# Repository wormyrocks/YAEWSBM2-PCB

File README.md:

# YAEWSBM2-PCB
PCBA for Dewster's Etherwave Standard bass extension module

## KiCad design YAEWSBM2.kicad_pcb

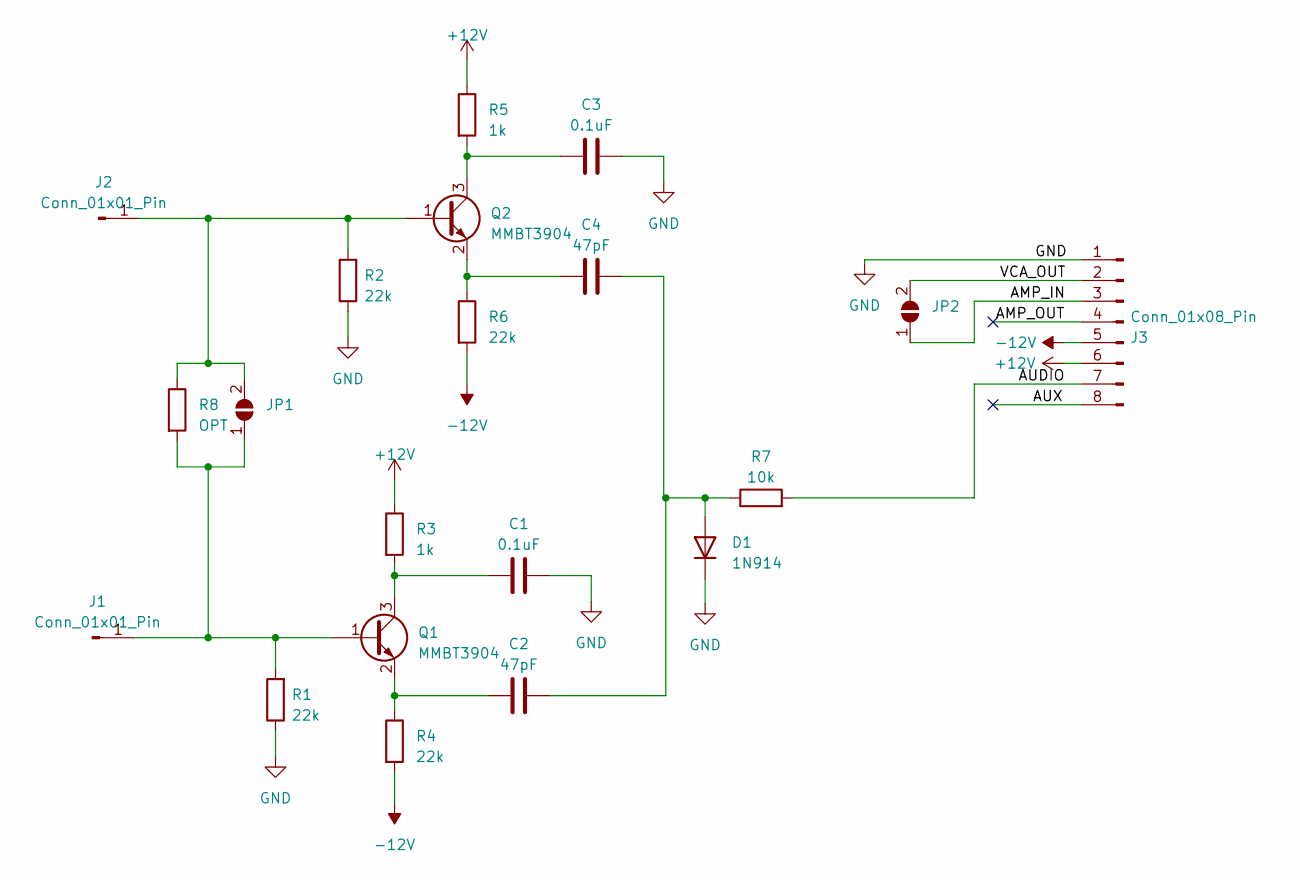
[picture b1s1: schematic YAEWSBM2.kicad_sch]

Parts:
C1, C3: 0.1uF; C_0603_1608Metric_Pad1.08x0.95mm_HandSolder
C2, C4: 47pF; C_0603_1608Metric_Pad1.08x0.95mm_HandSolder
D1: 1N914; D_SOD-523
J1, J2: Conn_01x01_Pin; PinHeader_1x01_P2.54mm_Vertical
J3: Conn_01x08_Pin; PinHeader_1x08_P2.54mm_Vertical
JP1, JP2: SolderJumper_2_Open; SolderJumper-2_P1.3mm_Open_RoundedPad1.0x1.5mm
Q1, Q2: MMBT3904; SOT-23
R1, R2, R4, R6: 22k; R_0603_1608Metric_Pad0.98x0.95mm_HandSolder
R3, R5: 1k; R_0603_1608Metric_Pad0.98x0.95mm_HandSolder
R7: 10k; R_0603_1608Metric_Pad0.98x0.95mm_HandSolder
R8: OPT; R_Axial_DIN0204_L3.6mm_D1.6mm_P5.08mm_Horizontal

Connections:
+12V: J3.6, R3.1, R5.1
-12V: J3.5, R4.2, R6.2
/AMP_IN: J3.3, JP2.1 (A)
/AMP_OUT: J3.4
/AUDIO: J3.7, R7.2
/AUX: J3.8
/VCA_OUT: J3.2, JP2.2 (B)
GND: C1.2, C3.2, D1.1 (K), J3.1, R1.1, R2.1
unnamed: C2.2, C4.2, D1.2 (A), R7.1
unnamed: J1.1, JP1.1 (A), Q1.1 (B), R1.2, R8.2
unnamed: J2.1, JP1.2 (B), Q2.1 (B), R2.2, R8.1
unnamed: C1.1, Q1.3 (C), R3.2
unnamed: C2.1, Q1.2 (E), R4.1
unnamed: C3.1, Q2.3 (C), R5.2
unnamed: C4.1, Q2.2 (E), R6.1

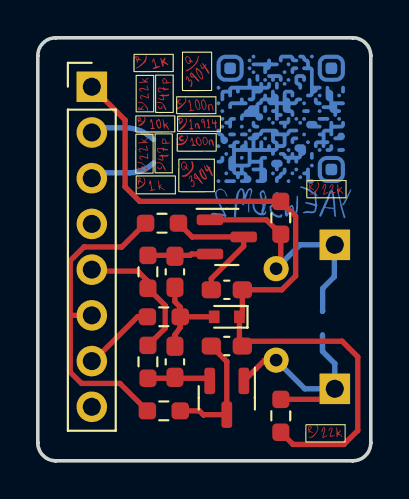
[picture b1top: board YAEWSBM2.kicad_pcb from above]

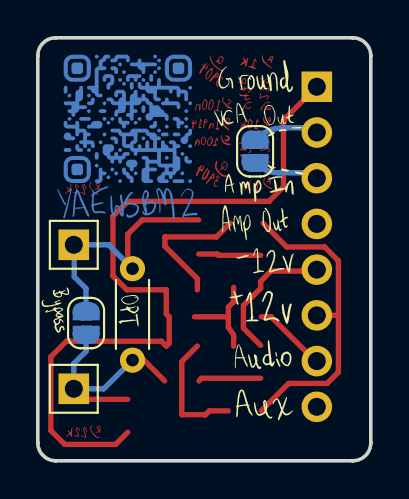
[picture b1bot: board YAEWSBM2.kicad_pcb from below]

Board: 2 copper layers, 18.5 x 23.5 mm, 20 parts (5 on the bottom side), 13 nets.

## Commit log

2023-01-15 Add files
2023-01-15 Add ibom
2023-01-30 silk art
